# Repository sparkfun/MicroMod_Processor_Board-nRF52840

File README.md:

SparkFun MicroMod Processor - nRF52840
========================================

[*SparkFun MicroMod Processor - nRF52840 (DEV-16984)*](https://www.sparkfun.com/products/16984)

Featuring the nRF52840 SoC from Nordic Semiconductor, the SparkFun MicroMod nRF52840 Processor offers a powerful combination of ARM Cortex-M4 CPU and 2.4 GHz Bluetooth transceiver in the MicroMod form-factor with the M.2 MicroMod connector to allow you to plug in a compatible MicroMod Carrier Board in the [MicroMod Ecosystem](https://www.sparkfun.com/micromod). 

The nRF52840 module includes a BT 5.1 stack and supports Bluetooth 5, Bluetooth mesh, IEEE 802.15.4 (Zigbee & Thread) and 2.4Ghz RF wireless protocols (including Nordic's proprietary RF protocol) allowing you to pick which option works best for your application. 

Repository Contents
-------------------

* **/Hardware** - Eagle design files (.brd, .sch)
* **/SF_MM_nRF52840_PB** - Board variant files for Arduino mbed Core.
* **/TestSketches** - Related software for the MicroMod nRF52840 Processor

Documentation
--------------

* **[Hookup Guide](https://learn.sparkfun.com/tutorials/micromod-nrf52840-processor-hookup-guide)** - Basic hookup guide for the MicroMod Processor - nRF52840.
* **[Getting Started with MicroMod](https://learn.sparkfun.com/tutorials/getting-started-with-micromod)** - A tutorial to help you get started with the MicroMod Ecosystem. 
* **[Designing with MicroMod](https://learn.sparkfun.com/tutorials/designing-with-micromod)** - A tutorial to walk you through the specs of the MicroMod processor and carrier board as well as the basics of incorporating the MicroMod form factor into your own PCB designs.
* **[SparkFun Graphical Datasheets](https://github.com/sparkfun/Graphical_Datasheets)** -Graphical Datasheets for various SparkFun products.

License Information
-------------------

This product is _**open source**_! 

Please review the LICENSE.md file for license information. 

If you have any questions or concerns on licensing, please contact technical support on our [SparkFun forums](https://forum.sparkfun.com/viewforum.php?f=152).

Distributed as-is; no warranty is given.

- Your friends at SparkFun.

_<COLLABORATION CREDIT>_

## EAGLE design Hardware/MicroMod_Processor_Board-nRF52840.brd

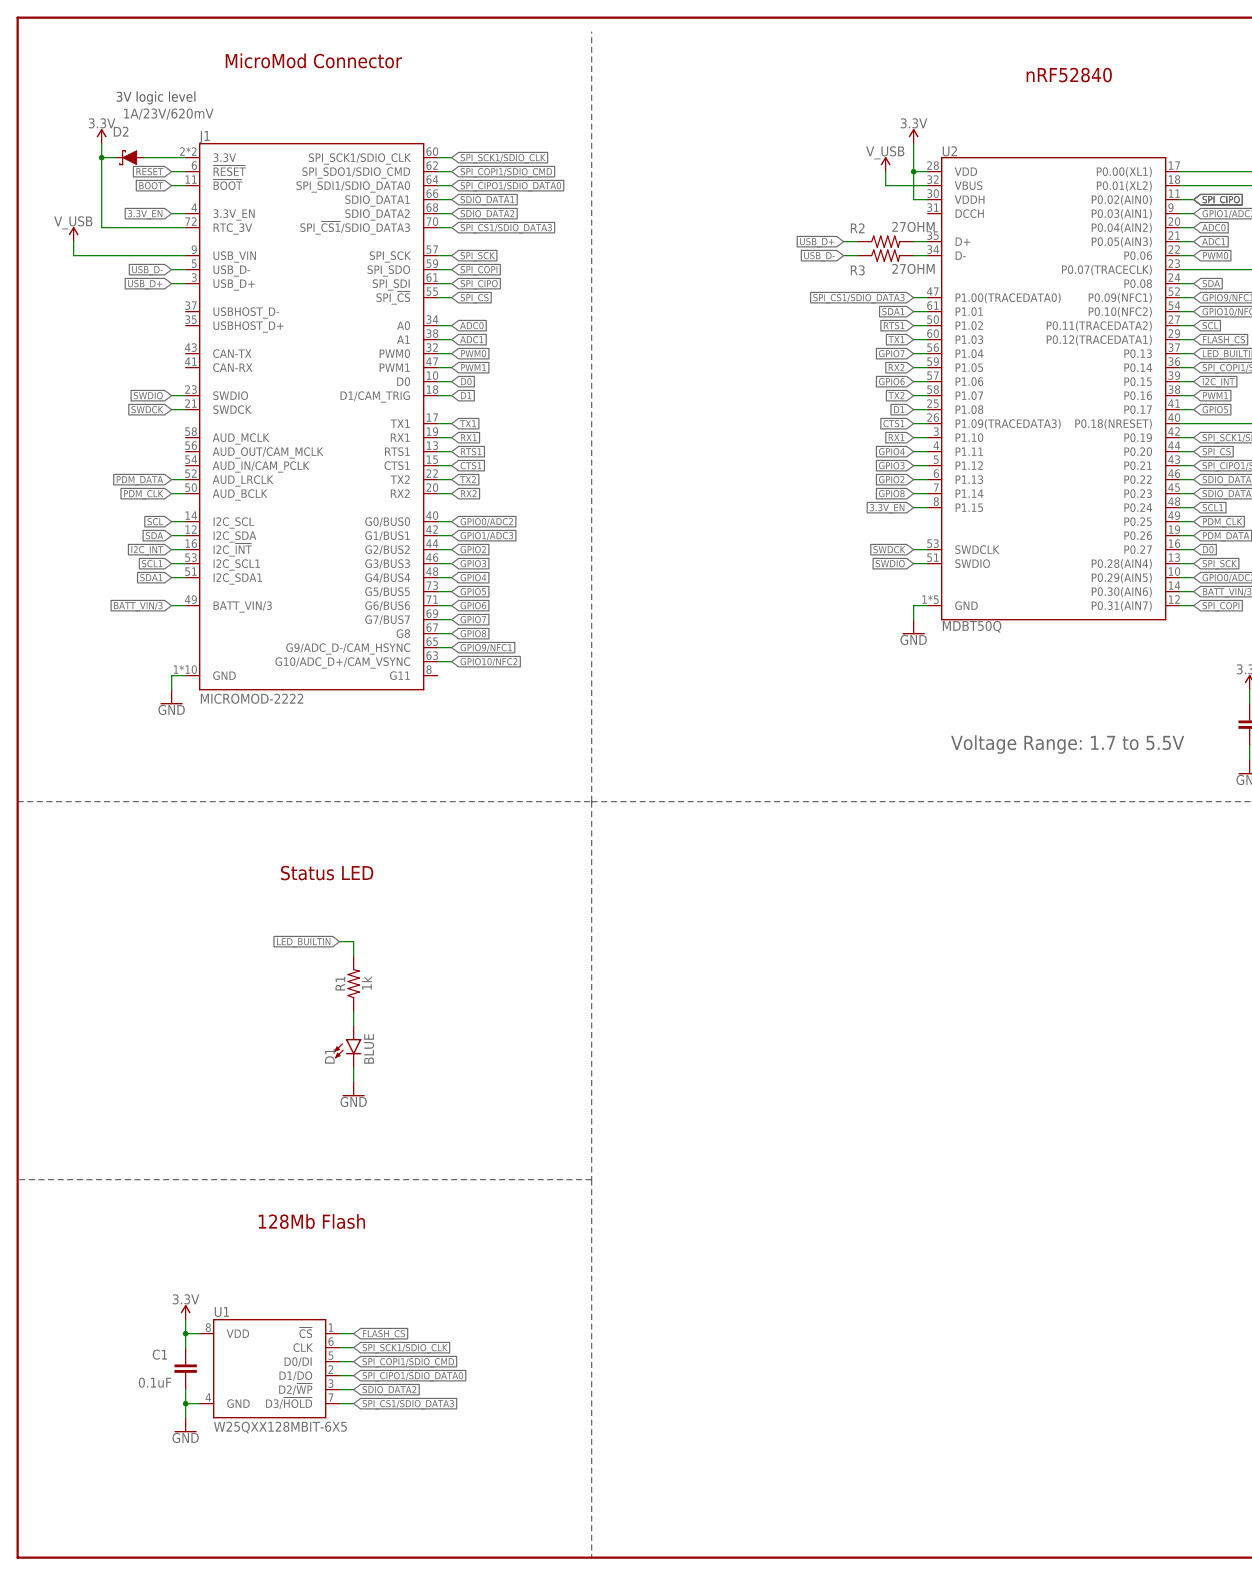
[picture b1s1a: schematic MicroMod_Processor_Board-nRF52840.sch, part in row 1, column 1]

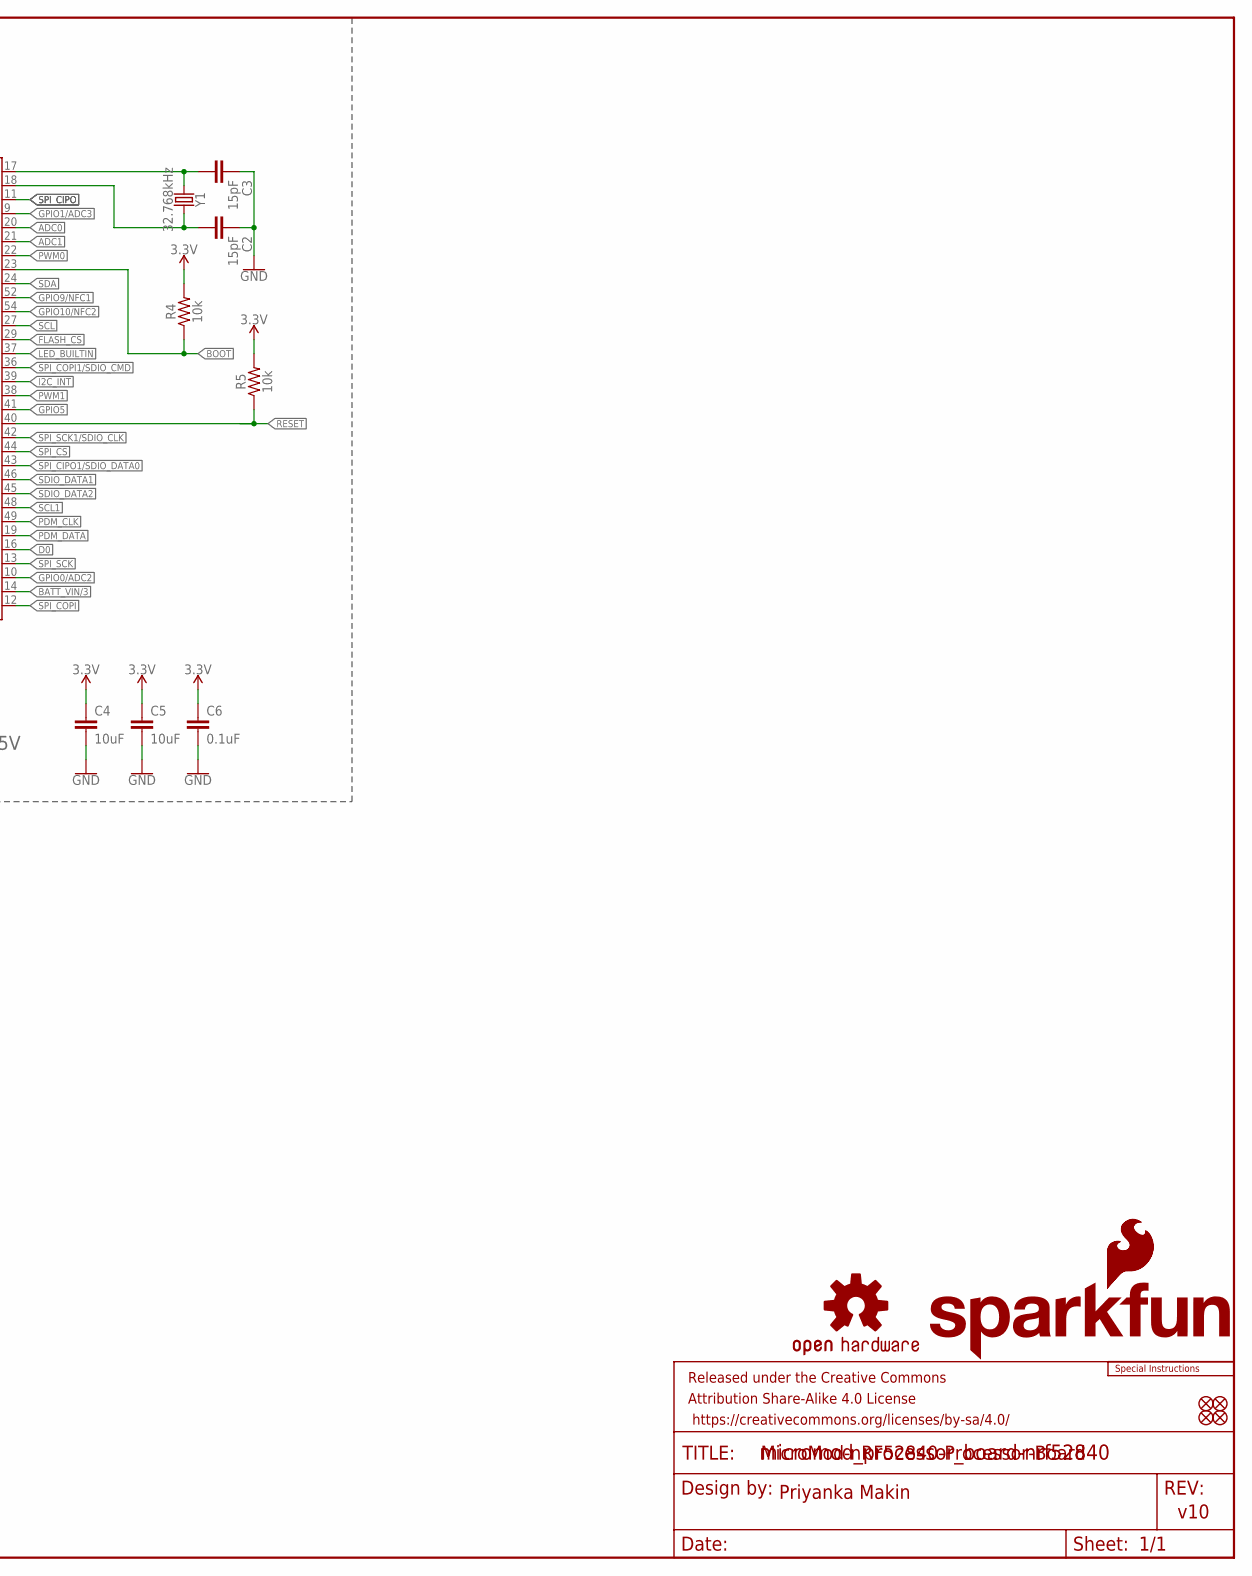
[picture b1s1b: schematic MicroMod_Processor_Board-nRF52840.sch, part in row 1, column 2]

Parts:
C1, C6: 0.1uF; 0402-TIGHT
C2, C3: 15pF; 0402-TIGHT
C4, C5: 10uF; 0402-TIGHT
D1: BLUE; LED-0603
D2: 1A/23V/620mV; SOD-323
FD1, FD2, FD3, FD4: FIDUCIALUFIDUCIAL; FIDUCIAL-MICRO
FRAME1: FRAME-LEDGER; CREATIVE_COMMONS
J1: MICROMOD-2222; M.2-CARD-E-22
LOGO1: SFE_LOGO_NAME_FLAME.1_INCH; SFE_LOGO_NAME_FLAME_.1
LOGO2: SFE_LOGO_FLAME.1_INCH; SFE_LOGO_FLAME_.1
LOGO3: OSHW-LOGOMINI; OSHW-LOGO-MINI
LOGO4: SPECIAL_INSTRUCTIONS-ORDERING; ORDERING_INSTRUCTIONS
R1: 1k; 0402-TIGHT
R2, R3: 27OHM; 0402-TIGHT
R4, R5: 10k; 0402-TIGHT
U1: W25QXX128MBIT-6X5; WSON-8-6X5
U2: MDBT50Q
Y1: 32.768kHz; CRYSTAL-SMD-3.2X1.5MM

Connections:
3.3V: C1.1, C4.1, C5.1, C6.1, D2.C, J1.72 (RTC_3V), R4.2, R5.2, U1.8 (VDD), U2.28 (VDD), U2.30 (VDDH)
3.3V_EN: J1.4 (3.3V_EN), U2.8 (P1.15)
!BOOT!: J1.11 (!BOOT!), R4.1, U2.23 (P0.07(TRACECLK))
!RESET!: J1.6 (!RESET!), R5.1, U2.40 (P0.18(NRESET))
ADC0: J1.34 (A0), U2.20 (P0.04(AIN2))
ADC1: J1.38 (A1), U2.21 (P0.05(AIN3))
BATT_VIN/3: J1.49 (BATT_VIN/3), U2.14 (P0.30(AIN6))
CTS1: J1.15 (CTS1), U2.26 (P1.09(TRACEDATA3))
D0: J1.10 (D0), U2.16 (P0.27)
D1: J1.18 (D1/CAM_TRIG), U2.25 (P1.08)
FLASH_!CS!: U1.1 (!CS!), U2.29 (P0.12(TRACEDATA1))
GND: C1.2, C2.1, C3.1, C4.2, C5.2, C6.2, D1.C, J1.1 (GND), J1.7 (GND), J1.33 (GND), J1.36 (GND), J1.39 (GND), J1.45 (GND), J1.75 (GND), J1.GND1 (GND), J1.GND2 (GND), J1.GND3 (GND), U1.4 (GND), U2.1 (GND), U2.2 (GND), U2.15 (GND), U2.33 (GND), U2.55 (GND)
GPIO0/ADC2: J1.40 (G0/BUS0), U2.10 (P0.29(AIN5))
GPIO1/ADC3: J1.42 (G1/BUS1), U2.9 (P0.03(AIN1))
GPIO2: J1.44 (G2/BUS2), U2.6 (P1.13)
GPIO3: J1.46 (G3/BUS3), U2.5 (P1.12)
GPIO4: J1.48 (G4/BUS4), U2.4 (P1.11)
GPIO5: J1.73 (G5/BUS5), U2.41 (P0.17)
GPIO6: J1.71 (G6/BUS6), U2.57 (P1.06)
GPIO7: J1.69 (G7/BUS7), U2.56 (P1.04)
GPIO8: J1.67 (G8), U2.7 (P1.14)
GPIO9/NFC1: J1.65 (G9/ADC_D-/CAM_HSYNC), U2.52 (P0.09(NFC1))
GPIO10/NFC2: J1.63 (G10/ADC_D+/CAM_VSYNC), U2.54 (P0.10(NFC2))
I2C_!INT!: J1.16 (I2C_!INT!), U2.39 (P0.15)
LED_BUILTIN: R1.2, U2.37 (P0.13)
unnamed: R2.2, U2.35 (D+)
unnamed: D1.A, R1.1
unnamed: R3.2, U2.34 (D-)
unnamed: C3.2, U2.17 (P0.00(XL1)), Y1.P$1 (1)
unnamed: D2.A, J1.2 (3.3V), J1.74 (3.3V)
unnamed: C2.2, U2.18 (P0.01(XL2)), Y1.P$2 (2)
PDM_CLK: J1.50 (AUD_BCLK), U2.49 (P0.25)
PDM_DATA: J1.52 (AUD_LRCLK), U2.19 (P0.26)
PWM0: J1.32 (PWM0), U2.22 (P0.06)
PWM1: J1.47 (PWM1), U2.38 (P0.16)
RTS1: J1.13 (RTS1), U2.50 (P1.02)
RX1: J1.19 (RX1), U2.3 (P1.10)
RX2: J1.20 (RX2), U2.59 (P1.05)
SCL: J1.14 (I2C_SCL), U2.27 (P0.11(TRACEDATA2))
SCL1: J1.53 (I2C_SCL1), U2.48 (P0.24)
SDA: J1.12 (I2C_SDA), U2.24 (P0.08)
SDA1: J1.51 (I2C_SDA1), U2.61 (P1.01)
SDIO_DATA1: J1.66 (SDIO_DATA1), U2.46 (P0.22)
SDIO_DATA2: J1.68 (SDIO_DATA2), U1.3 (D2/!WP!), U2.45 (P0.23)
SPI_!CS1!/SDIO_DATA3: J1.70 (SPI_!CS1!/SDIO_DATA3), U1.7 (D3/!HOLD!), U2.47 (P1.00(TRACEDATA0))
SPI_!CS!: J1.55 (SPI_!CS!), U2.44 (P0.20)
SPI_CIPO: J1.61 (SPI_SDI), U2.11 (P0.02(AIN0))
SPI_CIPO1/SDIO_DATA0: J1.64 (SPI_SDI1/SDIO_DATA0), U1.2 (D1/DO), U2.43 (P0.21)
SPI_COPI: J1.59 (SPI_SDO), U2.12 (P0.31(AIN7))
SPI_COPI1/SDIO_CMD: J1.62 (SPI_SDO1/SDIO_CMD), U1.5 (D0/DI), U2.36 (P0.14)
SPI_SCK: J1.57 (SPI_SCK), U2.13 (P0.28(AIN4))
SPI_SCK1/SDIO_CLK: J1.60 (SPI_SCK1/SDIO_CLK), U1.6 (CLK), U2.42 (P0.19)
SWDCK: J1.21 (SWDCK), U2.53 (SWDCLK)
SWDIO: J1.23 (SWDIO), U2.51 (SWDIO)
TX1: J1.17 (TX1), U2.60 (P1.03)
TX2: J1.22 (TX2), U2.58 (P1.07)
USB_D+: J1.3 (USB_D+), R2.1
USB_D-: J1.5 (USB_D-), R3.1
V_USB: J1.9 (USB_VIN), U2.32 (VBUS)

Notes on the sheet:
MicroMod Connector
Status LED
MicroMod-nRF52840-Processor-Board
Priyanka Makin
v10
128Mb Flash
Voltage Range: 1.7 to 5.5V
nRF52840
3V logic level

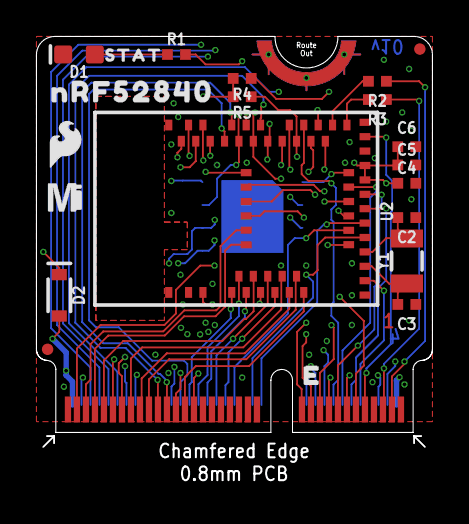
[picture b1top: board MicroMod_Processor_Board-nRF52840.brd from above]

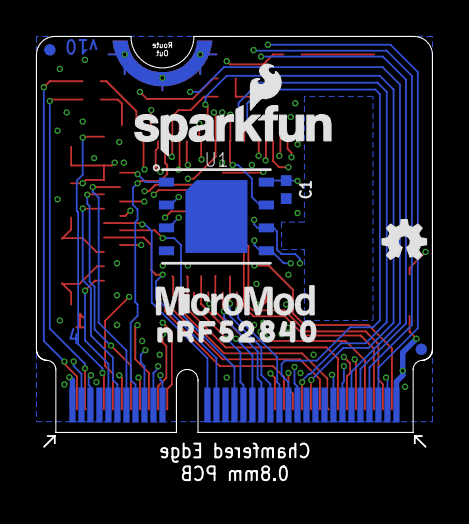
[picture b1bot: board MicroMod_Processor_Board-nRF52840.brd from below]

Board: 4 copper layers, 22.0 x 22.8 mm, 31 parts (8 on the bottom side), 59 nets.

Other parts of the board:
U$1: MICROMOD_MI_LOGO_.35
U$2: STAT0
U$3, U$6: NRF528400
U$5: MICROMOD_LOGO_.35

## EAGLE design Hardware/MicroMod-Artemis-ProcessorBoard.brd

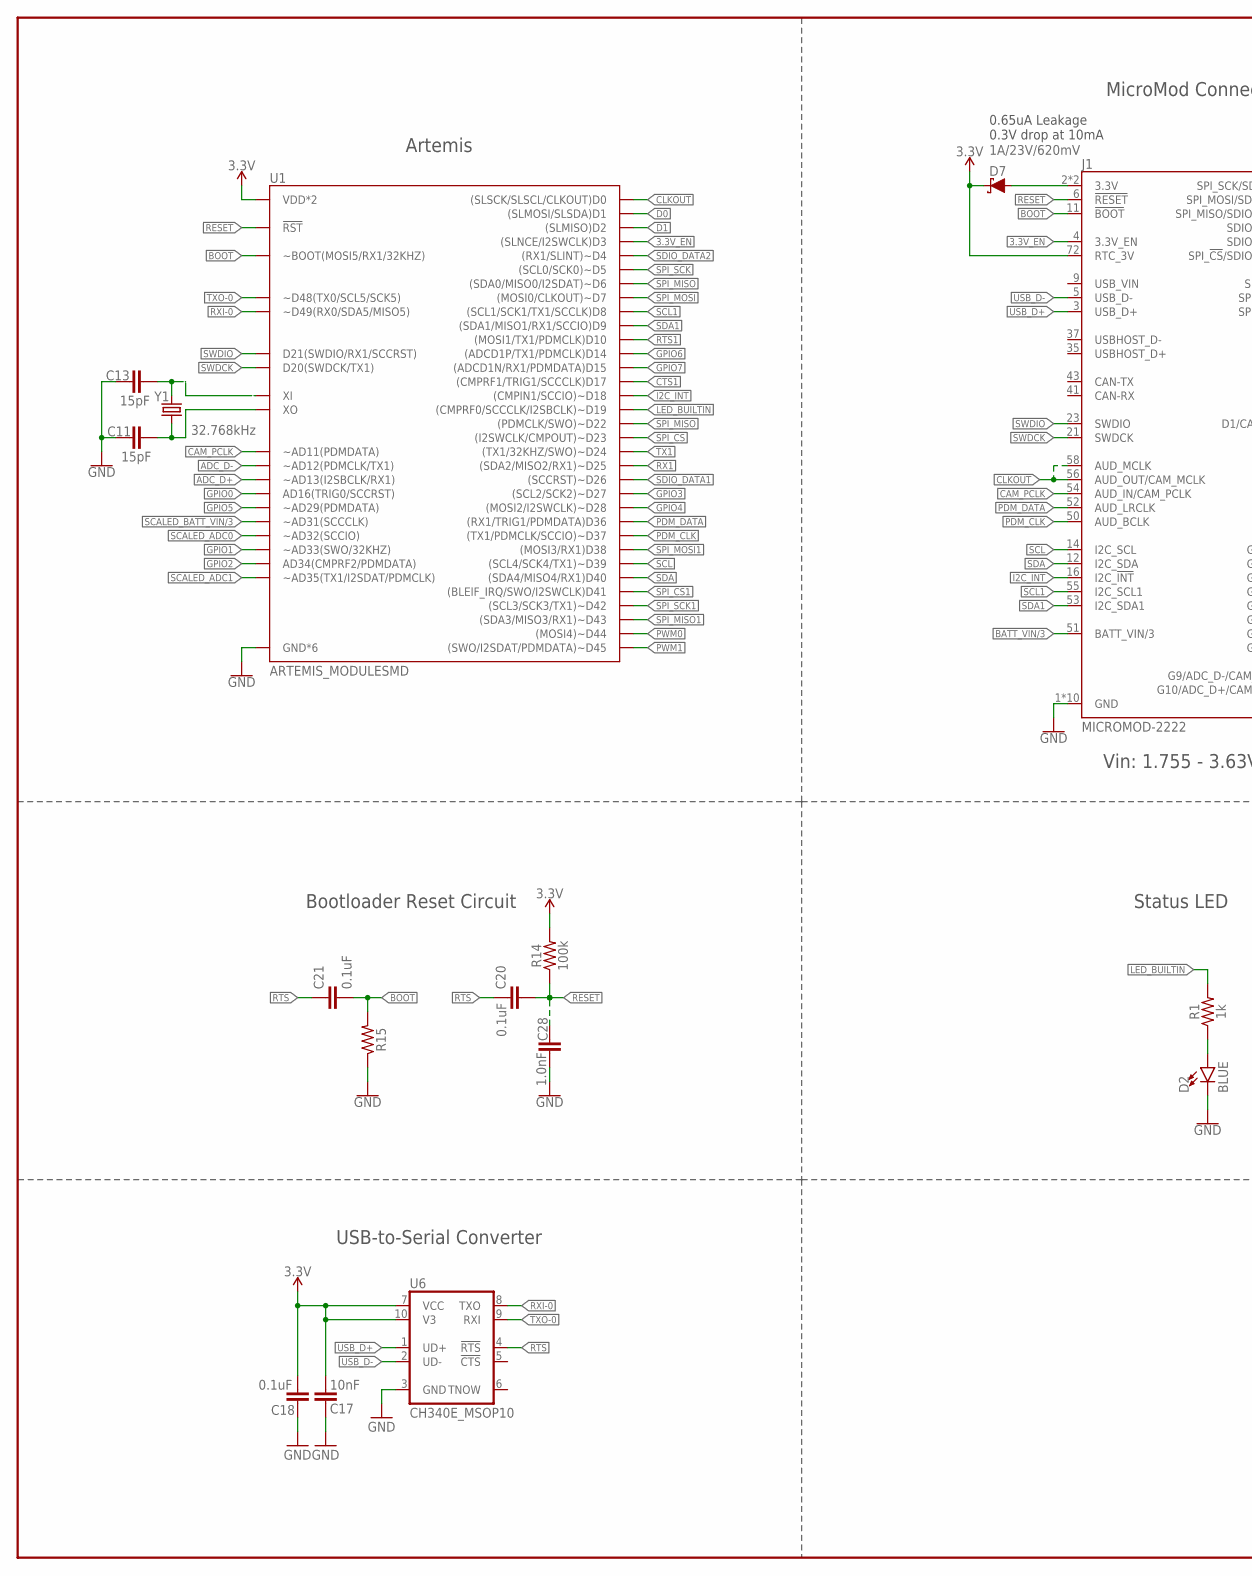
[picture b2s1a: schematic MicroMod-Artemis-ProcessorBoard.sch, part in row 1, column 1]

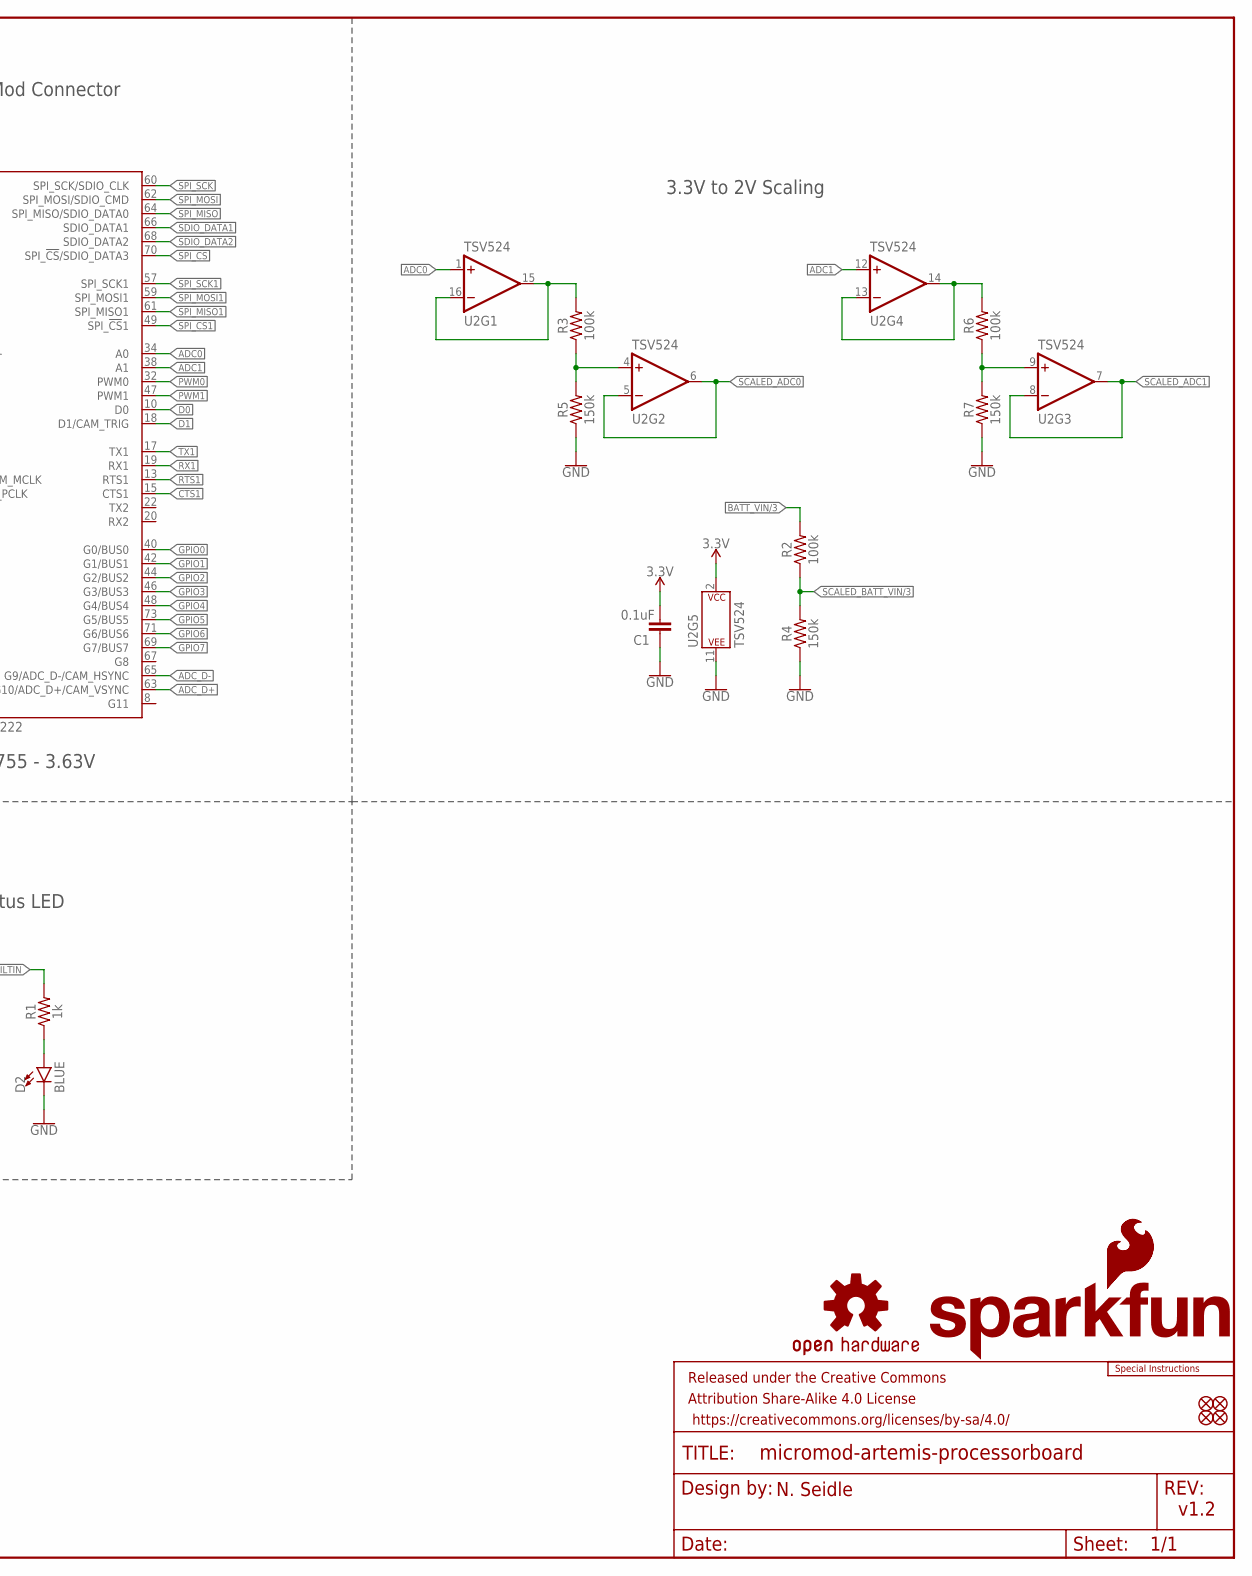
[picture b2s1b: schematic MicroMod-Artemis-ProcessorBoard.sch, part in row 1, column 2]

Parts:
C1, C18, C20, C21: 0.1uF; 0402-TIGHT
C11, C13: 15pF; 0402-TIGHT
C17: 10nF; 0402-TIGHT
C28: 1.0nF; 0402-TIGHT
D2: BLUE; LED-0603
D7: 1A/23V/620mV; SOD-323
FD1, FD2, FD3, FD4: FIDUCIALUFIDUCIAL; FIDUCIAL-MICRO
FRAME1: FRAME-LEDGER; CREATIVE_COMMONS
J1: MICROMOD-2222; M.2-CARD-E-22
LOGO1: SFE_LOGO_NAME_FLAME.1_INCH; SFE_LOGO_NAME_FLAME_.1
LOGO2: SFE_LOGO_FLAME.1_INCH; SFE_LOGO_FLAME_.1
LOGO3: OSHW-LOGOMINI; OSHW-LOGO-MINI
LOGO4: SPECIAL_INSTRUCTIONS-ORDERING; ORDERING_INSTRUCTIONS
R1: 1k; 0402-TIGHT
R2, R3, R6, R14: 100k; 0402-TIGHT
R4, R5, R7: 150k; 0402-TIGHT
R15: 220KOHM-0402T-1/16W-1%; 0402-TIGHT
U1: ARTEMIS_MODULESMD; ARTEMIS_FP
U2: TSV524; QFN-16
U6: CH340E_MSOP10; MSOP10
Y1: 32.768kHz; CRYSTAL-SMD-3.2X1.5MM

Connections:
3.3V: C1.1, C17.1, C18.1, D7.C, J1.72 (RTC_3V), R14.2, U1.VDD@36 (VDD*2), U1.VDD@37 (VDD*2), U2.2 (V+), U6.7 (VCC), U6.10 (V3)
3.3V_EN: J1.4 (3.3V_EN), U1.D3 ((SLNCE/I2SWCLK)D3)
3.3V_MAIN: D7.A, J1.2 (3.3V), J1.74 (3.3V)
!RESET!: C20.2, C28.1, J1.6 (!RESET!), R14.1, U1.~RST (!RST)
!RTS: C20.1, C21.1, U6.4 (!RTS)
ADC0: J1.34 (A0), U2.1 (+IN)
ADC0_BUFF1: R3.2, U2.15 (OUT), U2.16 (-IN)
ADC0_BUFF2: R3.1, R5.2, U2.4 (+IN)
ADC1: J1.38 (A1), U2.12 (+IN)
ADC1_BUFF2: R6.1, R7.2, U2.9 (+IN)
ADC_BUFF1: R6.2, U2.13 (-IN), U2.14 (OUT)
ADC_D+: J1.63 (G10/ADC_D+/CAM_VSYNC), U1.~AD13 (~AD13(I2SBCLK/RX1))
ADC_D-: J1.65 (G9/ADC_D-/CAM_HSYNC), U1.~AD12 (~AD12(PDMCLK/TX1))
BATT_VIN/3: J1.51 (BATT_VIN/3), R2.2
BOOT: C21.2, J1.11 (!BOOT!), R15.2, U1.BOOT (~BOOT(MOSI5/RX1/32KHZ))
CAM_PCLK: J1.54 (AUD_IN/CAM_PCLK), U1.~AD11 (~AD11(PDMDATA))
CLKOUT: J1.56 (AUD_OUT/CAM_MCLK), J1.58 (AUD_MCLK), U1.D0 ((SLSCK/SLSCL/CLKOUT)D0)
CTS1: J1.15 (CTS1), U1.D17 ((CMPRF1/TRIG1/SCCCLK)D17)
D0: J1.10 (D0), U1.D1 ((SLMOSI/SLSDA)D1)
D1: J1.18 (D1/CAM_TRIG), U1.D2 ((SLMISO)D2)
GND: C1.2, C11.1, C13.1, C17.2, C18.2, C28.2, D2.C, J1.1 (GND), J1.7 (GND), J1.33 (GND), J1.36 (GND), J1.39 (GND), J1.45 (GND), J1.75 (GND), J1.GND1 (GND), J1.GND2 (GND), J1.GND3 (GND), R4.1, R5.1, R7.1, R15.1, U1.GND@1 (GND*6), U1.GND@22 (GND*6), U1.GND@38 (GND*6), U1.GND@39 (GND*6), U1.GND@47 (GND*6), U1.GND@59 (GND*6), U2.11 (V-), U6.3 (GND)
GPIO0: J1.40 (G0/BUS0), U1.AD16 (AD16(TRIG0/SCCRST))
GPIO1: J1.42 (G1/BUS1), U1.~AD33/SWO (~AD33(SWO/32KHZ))
GPIO2: J1.44 (G2/BUS2), U1.AD34 (AD34(CMPRF2/PDMDATA))
GPIO3: J1.46 (G3/BUS3), U1.~D27 ((SCL2/SCK2)~D27)
GPIO4: J1.48 (G4/BUS4), U1.~D28 ((MOSI2/I2SWCLK)~D28)
GPIO5: J1.73 (G5/BUS5), U1.~AD29 (~AD29(PDMDATA))
GPIO6: J1.71 (G6/BUS6), U1.D14 ((ADCD1P/TX1/PDMCLK)D14)
GPIO7: J1.69 (G7/BUS7), U1.D15 ((ADCD1N/RX1/PDMDATA)D15)
I2C_!INT!: J1.16 (I2C_!INT!), U1.~D18 ((CMPIN1/SCCIO)~D18)
LED_BUILTIN: R1.2, U1.~D19 ((CMPRF0/SCCCLK/I2SBCLK)~D19)
unnamed: D2.A, R1.1
unnamed: C13.2, Y1.P$1 (1)
unnamed: C11.2, U1.XO, Y1.P$2 (2)
PDM_CLK: J1.50 (AUD_BCLK), U1.~D37 ((TX1/PDMCLK/SCCIO)~D37)
PDM_DATA: J1.52 (AUD_LRCLK), U1.D36 ((RX1/TRIG1/PDMDATA)D36)
PWM0: J1.32 (PWM0), U1.~D44 ((MOSI4)~D44)
PWM1: J1.47 (PWM1), U1.~D45 ((SWO/I2SDAT/PDMDATA)~D45)
RTS1: J1.13 (RTS1), U1.D10 ((MOSI1/TX1/PDMCLK)D10)
RX1: J1.19 (RX1), U1.~D25 ((SDA2/MISO2/RX1)~D25)
RXI-0: U1.RXI-0 (~D49(RX0/SDA5/MISO5)), U6.8 (TXO)
SCALED_ADC0: U1.~AD32 (~AD32(SCCIO)), U2.5 (-IN), U2.6 (OUT)
SCALED_ADC1: U1.~AD35 (~AD35(TX1/I2SDAT/PDMCLK)), U2.7 (OUT), U2.8 (-IN)
SCALED_BATT_VIN/3: R2.1, R4.2, U1.~AD31 (~AD31(SCCCLK))
SCL: J1.14 (I2C_SCL), U1.~D39 ((SCL4/SCK4/TX1)~D39)
SCL1: J1.55 (I2C_SCL1), U1.D8 ((SCL1/SCK1/TX1/SCCLK)D8)
SDA: J1.12 (I2C_SDA), U1.D40 ((SDA4/MISO4/RX1)D40)
SDA1: J1.53 (I2C_SDA1), U1.D9 ((SDA1/MISO1/RX1/SCCIO)D9)
SDIO_DATA1: J1.66 (SDIO_DATA1), U1.~D26 ((SCCRST)~D26)
SDIO_DATA2: J1.68 (SDIO_DATA2), U1.~D4 ((RX1/SLINT)~D4)
SPI_!CS!: J1.70 (SPI_!CS!/SDIO_DATA3), U1.~D23 ((I2SWCLK/CMPOUT)~D23)
SPI_!CS!1: J1.49 (SPI_!CS!1), U1.D41 ((BLEIF_IRQ/SWO/I2SWCLK)D41)
SPI_MISO: J1.64 (SPI_MISO/SDIO_DATA0), U1.~D6 ((SDA0/MISO0/I2SDAT)~D6), U1.~D22 ((PDMCLK/SWO)~D22)
SPI_MISO1: J1.61 (SPI_MISO1), U1.~D43 ((SDA3/MISO3/RX1)~D43)
SPI_MOSI: J1.62 (SPI_MOSI/SDIO_CMD), U1.D7 ((MOSI0/CLKOUT)~D7)
SPI_MOSI1: J1.59 (SPI_MOSI1), U1.D38 ((MOSI3/RX1)D38)
SPI_SCK: J1.60 (SPI_SCK/SDIO_CLK), U1.~D5 ((SCL0/SCK0)~D5)
SPI_SCK1: J1.57 (SPI_SCK1), U1.~D42 ((SCL3/SCK3/TX1)~D42)
SWDCK: J1.21 (SWDCK), U1.SWDCK (D20(SWDCK/TX1))
SWDIO: J1.23 (SWDIO), U1.SWDIO (D21(SWDIO/RX1/SCCRST))
TX1: J1.17 (TX1), U1.~D24 ((TX1/32KHZ/SWO)~D24)
TXO-0: U1.TXO-0 (~D48(TX0/SCL5/SCK5)), U6.9 (RXI)
USB_D+: J1.3 (USB_D+), U6.1 (UD+)
USB_D-: J1.5 (USB_D-), U6.2 (UD-)

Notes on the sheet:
USB-to-Serial Converter
Bootloader Reset Circuit
MicroMod Connector
3.3V to 2V Scaling
v1.2
N. Seidle
Artemis
Status LED
Vin: 1.755 - 3.63V
0.65uA Leakage 0.3V drop at 10mA

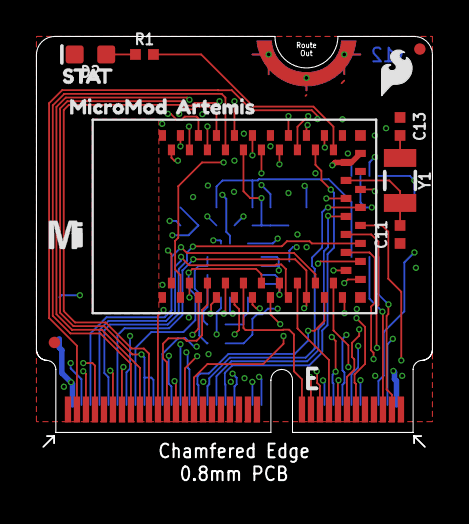
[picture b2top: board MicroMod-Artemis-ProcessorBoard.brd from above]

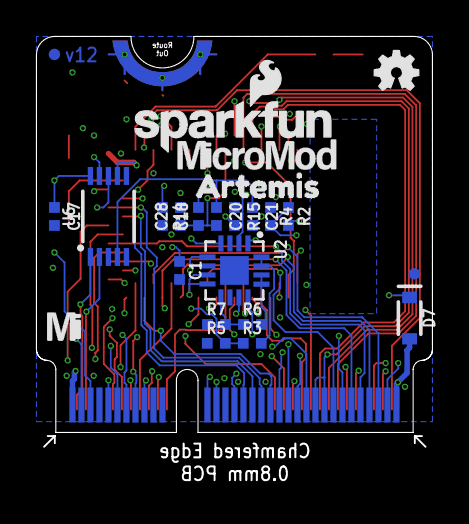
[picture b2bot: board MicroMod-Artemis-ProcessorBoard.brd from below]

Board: 4 copper layers, 22.0 x 22.8 mm, 40 parts (24 on the bottom side), 64 nets.

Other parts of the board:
U$1, U$7: MICROMOD_MI_LOGO_.35
U$2: ARTEMIS0
U$3: MICROMOD1
U$4: STAT_TO_32
U$5: MICROMOD_LOGO_.35
U$6: ARTEMIS2

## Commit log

2020-06-04 Initial commit
    Copied Artemis PB Eagle files into repo as a starting point.
2020-06-04 Renamed eagle files appropriately
2020-06-09 Ripped up old traces
2020-06-09 Removed some dividing lines in schematic
2020-06-17 Determined nets of some nRF pins.
2020-06-19 Working on schematic
2020-06-19 Preliminary schematic finished
2020-06-23 Finished preliminary schematic
2020-06-24 Preliminary layout of PB
2020-07-14 Started routing
2020-07-14 Routing
2020-07-23 Placed silk screen
2020-07-25 Implemented changes from first design review
2020-07-27 Going over check list
2020-07-29 Changes from QC Double Check
2020-07-30 Added more GND vias and made top polygon isolate larger
2020-07-30 Firt panelization and cam generation
2020-09-01 Initial variant commit
2020-09-09 Adding temp folder that holds current variant files
2020-09-15 Update variant
2020-09-15 update variant file
2020-09-16 Working on QSPI
2020-09-17 Define PDM pins
2020-09-24 New variant files for arduino core
2020-09-24 Updating variant file
2020-09-29 mbed core, variant files
2020-09-29 Messing with variants
2020-09-29 Move variants
2020-09-29 Variants
2020-10-01 Schematic updated post-proto testing
    Changes made: https://docs.google.com/document/d/1057ZJf50zAkChxiBm4WqtqCuvZdJMlmnGmuK_T1RHvQ/edit
2020-10-01 Routing for v10
2020-10-02 Design review and checklist changes
2020-10-06 Get variants the same across computers
2020-10-06 Updating variant files, ble demo
2020-10-07 Update ble_temp.ino
    Created BLE example demo/use case for nRF PB. TX BME280 temperature measurements.
2020-10-07 Update PROD_IDs for 27 ohm resistors
2020-10-08 Re-panelized for v10
2020-10-13 Update MicroMod_Processor_Board-nRF52840.zip
    New board files for v10
2020-10-29 Updated variant files and moved examples to dedicated folder
2020-11-05 Analog pin defs
2020-11-06 Updated variant files for new version of arduino core
2020-11-09 Renamed variant files and updated boards.txt
2020-11-09 Cleaned up variant files
2020-11-10 Clean up variant files
    Review with Paul
2020-12-21 Initial README commit
    Adding README for nRF Processor
2021-01-14 Update README.md
    Fix folder name and description for Variant Files. Add link to MicroMod landing page.
2021-02-25 updating ble_temp example
2022-04-07 Updates for "Arduino Mbed OS Nano Boards" v3.0.1
2022-06-09 Remove excess variant files.
    From now on, we want customers to duplicate the "ARDUINO_NANO33BLE" folder of the arduino board package, rename it to "SF_MM_nRF52840_PB", and only copy over the MM specific pin definition files. Thi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

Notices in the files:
parts and their libraries:
SparkFun-IC-Microcontroller: Licensing: Creative Commons ShareAlike 4.0 International - https://creativecommons.org/licenses/by-sa/4.0
SparkFun-Aesthetics: Released under the Creative Commons Attribution Share-Alike 4.0 License
SparkFun-Aesthetics: https://creativecommons.org/licenses/by-sa/4.0
